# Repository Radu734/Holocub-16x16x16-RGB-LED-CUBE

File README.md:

# **Holocub V2 – 16×16×16 RGB LED Cube**

*A fully addressable 3D LED display for animations, games, and visual effects.*

---

## 📜 Overview
Holocub V2 is a large-scale **16×16×16 RGB LED cube** (4096 voxels total) built with WS2812B addressable LEDs.  
It is designed to display dynamic animations, interactive effects, and data visualizations in 3D.

The cube is controlled by a microcontroller (planned: **RPi Pico 2W / other capable MCU**) and supports both **procedural animations** and **pre-rendered frames** loaded from an SD card.

---

## 🔧 Hardware Specifications

| Component                     | Specification |
|--------------------------------|---------------|
| **Cube Size**                 | 16 × 16 × 16 voxels |
| **Total LEDs**                | 4096 WS2812B RGB LEDs |
| **LED Type**                  | WS2812B (5V, individually addressable) |
| **PSUs**                      | 4 × 5v 350w |
| **Data Lines**                | One per 16×16 vertical layer (16 total) |
| **LED Strip Arrangement**     | Snake layout per layer (serpentine wiring) |
| **MCU**                       | Raspberry Pi Pico 2W (planned) / Teensy 4.1 (more power but no internal BLE and wifi) |
| **Storage**                   | MicroSD card (frame/animation storage) |
| **Power Injection**           | Multiple injection points per strip |
| **Estimated Max Power**       | ~1.23 kW at full white (theoretical max) |

---

# HoloBoard – PCB by Dragoș

**Short description**  
HoloBoard is a custom PCB designed for the Holocub project, acting as the main control and interface board.  
It hosts a Raspberry Pi Pico 2W, integrates a piezo buzzer, and features two bidirectional logic-level shifters for for the communication between the pico and the WS2812B as 3v3 logic could cause interference.

## 🔧 Key Features
- **MCU Slot:** Raspberry Pi Pico 2W header footprint (solder-in or socket).
- **Audio Output:** 1 × piezo buzzer connector (with optional series resistor).
- **Expandable hardware:** Left over pins (used mainly for I²C and SPI) routed to the side for extra connectivity.
- **Build Quality:** Silk labels for pins, test pads, and mounting holes.
- **Filter capacitors:** 2 filter caps for main power connection and 1 for each logic level shofter for optimal data transmission without interference.

## 📦 Minimal BOM
- 1 × RP2040 (Pico 2W) socket / header footprint
- Headers, pads, mounting hardware
- Yet to add more info

---

## 📜 Schematics & Photos

### **Schematic – Level Shifter**
  
*Figure 1 — The HoloBoard schematic in KeyCad.*

### **Schematic – Power & Buzzer**
  
*Figure 2 — components used, I/O's, connections.*

### **Photo – Assembled (Front)**
  
*Figure 3 — Front view, Pico 2W inserted.*

### **Photo – Assembled (Back / Solder Side)**
  
*Figure 4 — Back view showing soldering and Logo.*

---

## 🚀 Features
- **Scalable architecture** – animations work on both 4×4×4 test cube and full 16×16×16 cube. 
- **Voxel-based rendering** – uses a global `voxelMatrix[x][y][z]` buffer for color control.
- **Procedural animations** – gradients, bouncing “DVD logo” effect, rain simulation, waves.
- **Pre-rendered playback** – read `.vox` file for animations or custom binary format.
- **Custom GFX library** – draw lines, planes, waves, text in 3D space.
- **SD card support** – load animations without reflashing firmware.
- **Multi-PSU design** – independent PSU per cube tower for stable power delivery.
- **Website based animation upload and debug** - Upload animations or images directly from a computer to the Holocube.

---

## ⚡ Power & Safety Notes
- WS2812B LEDs consume up to **60 mA per LED** at full brightness (white).
- Theoretical maximum current: **~245 A total** across 4 PSUs.
- Always fuse PSU outputs and use thick wiring for high-current paths.
- Avoid running full white at 100% brightness for prolonged periods to reduce heat.

---

## 🖥️ Software Workflow
### **Procedural animations**
- Written in C++ inside `/animations`
- Rendered directly to `voxelMatrix`
- Useful for dynamic effects and parameterized visuals

### **Pre-rendered animations**
- Created in Paint, MagicaVoxel, or similar tools
- Exported as `.bmp` or custom `.hca` (Holocub Animation) binary format
- Loaded via SD card at runtime

---

## 📸 Development Timeline
- **Phase 1** – Test code, Custom PCB `HoloBoard`, SD card reader on 4×4×4 cube ✅
- **Phase 2** – Develop GFX & cube configuration libraries ✅
- **Phase 3** – Build cube structure & solder all LED strips 🔄
- **Phase 4** – Integrate procedural + SD-based playback
- **Phase 5** – Optimize power, stability, and animation library

---

## 🛠️ Setup & Build
### **Dependencies**
- [Adafruit NeoPixel](https://github.com/adafruit/Adafruit_NeoPixel)
- SD card library for chosen MCU
- C++17 compatible toolchain
- PlatformIO (recommended) or Arduino IDE

### **Compilation**
```bash
# PlatformIO
pio run --target upload
```

### **Arduino IDE**
- Install Adafruit NeoPixel library
- Select **Raspberry Pi Pico 2W** (or your MCU)
- Upload `src/main.ino`

---

## 📄 License
[MIT License](LICENSE) – You are free to use, modify, and distribute this project with attribution.

---

## 🙌 Credits
- **Core team:** [Bernea Dragoș Dada & Teodosiu Radu]
- **Special thanks:** MaltWiskey (inspiration & reference designs), Adafruit (NeoPixel library) and the C++ community.
- **Open Source softwares used for the cube animations:** MagicaVoxel (3D sprites designer)

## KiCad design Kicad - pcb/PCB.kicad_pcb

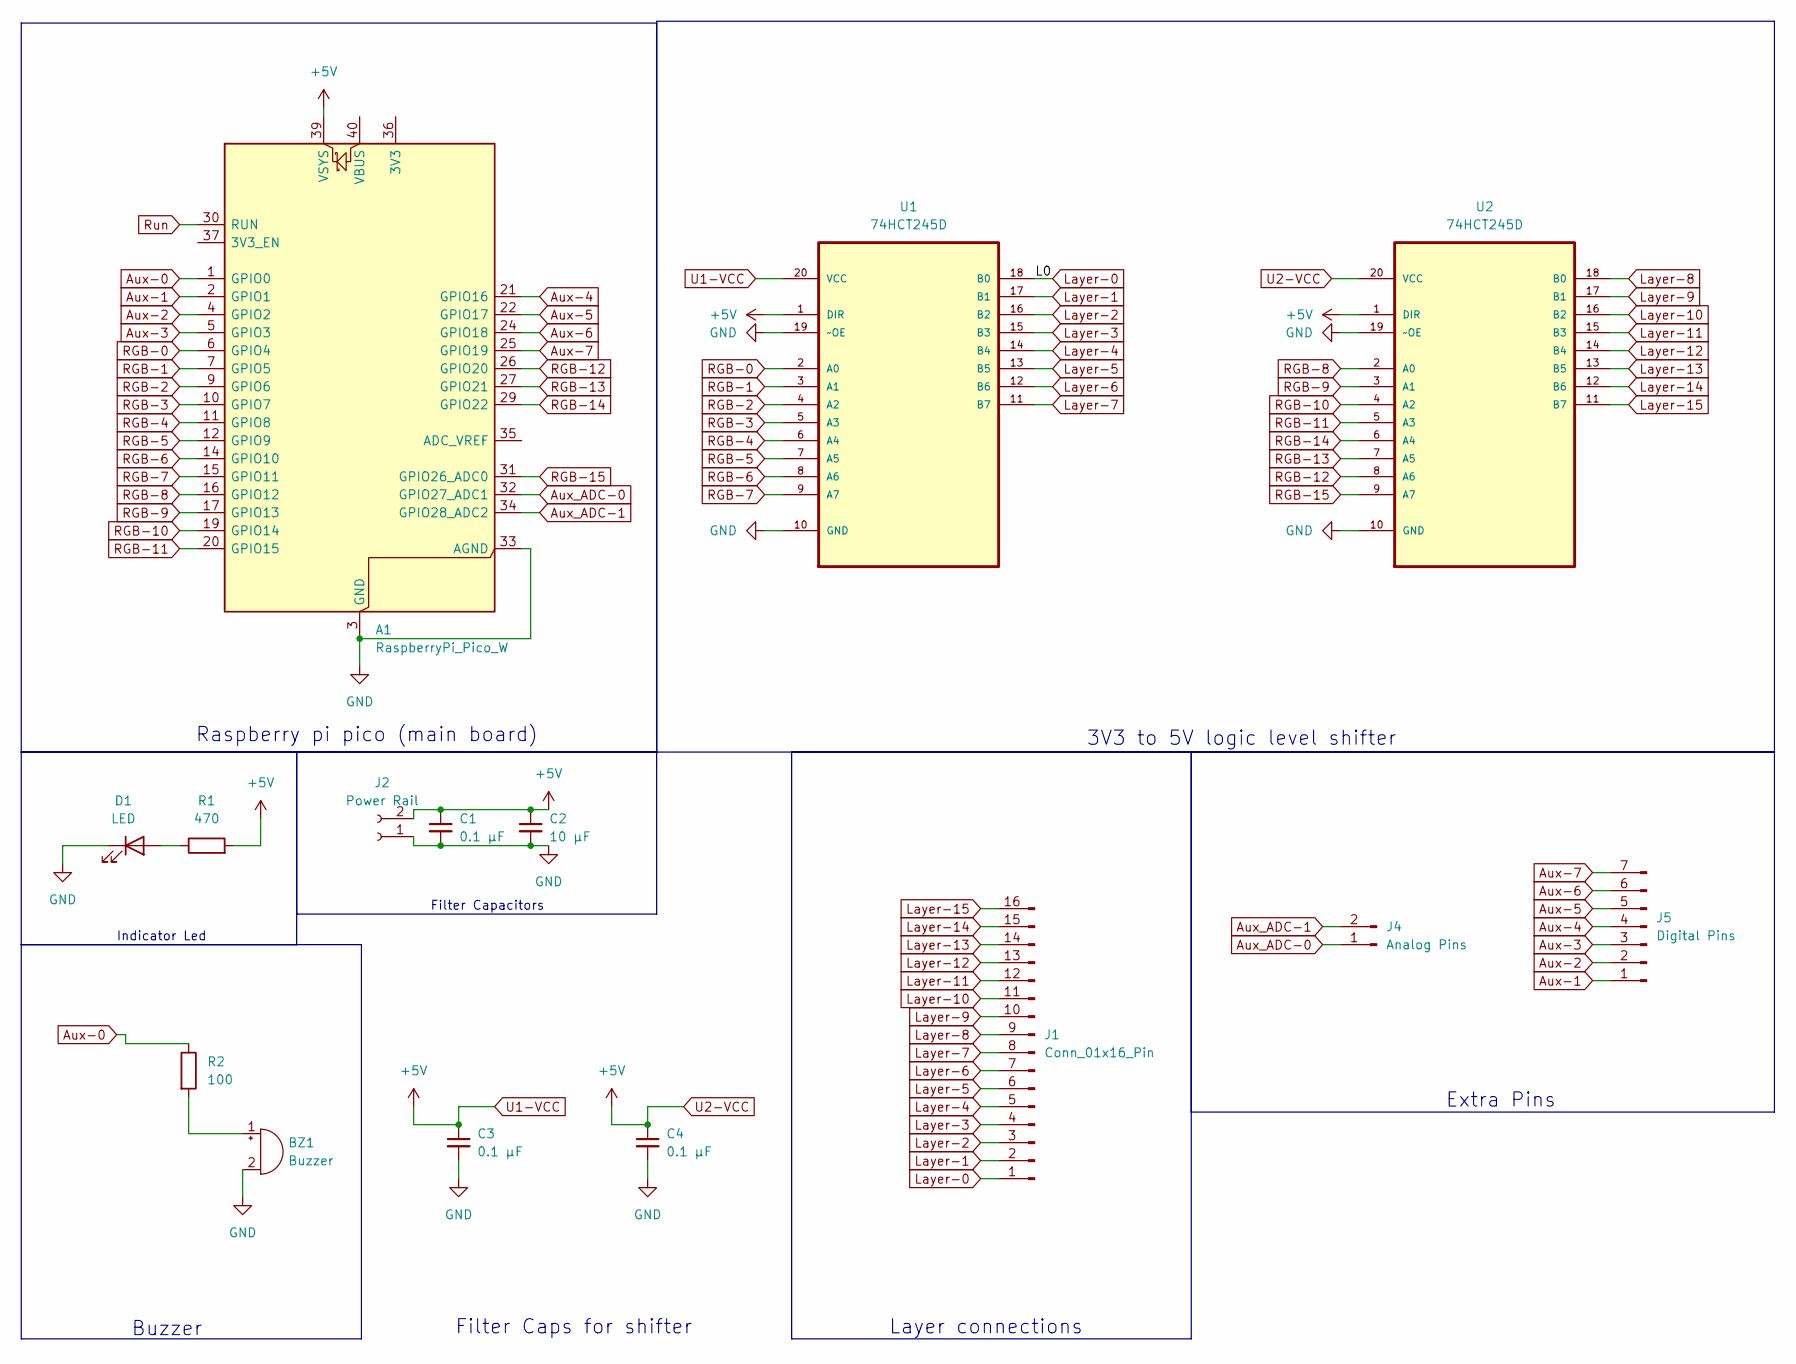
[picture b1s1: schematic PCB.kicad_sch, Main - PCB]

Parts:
A1: RaspberryPi_Pico_W; RaspberryPi_Pico_Common_THT
BZ1: Buzzer; Buzzer_12x9.5RM7.6
C1: 0.1 µF; C_0603_1608Metric
C2: 10 µF; C_1206_3216Metric
C3, C4: 0.1 µF; C_0201_0603Metric
D1: LED; LED_0603_1608Metric_Pad1.05x0.95mm_HandSolder
J1: Conn_01x16_Pin; PinHeader_1x16_P2.54mm_Vertical
J2: Power Rail; PinHeader_1x02_P2.54mm_Vertical
J4: Analog Pins; PinHeader_1x02_P2.54mm_Vertical
J5: Digital Pins; PinHeader_1x07_P2.54mm_Vertical
R1: 470; R_0201_0603Metric
R2: 100; R_0603_1608Metric
U1, U2: 74HCT245D; SOIC127P1032X265-20N; MPN 74HCT245D

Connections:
Aux-0: A1.1 (GPIO0), R2.1
Aux-1: A1.2 (GPIO1), J5.1
Aux-2: A1.4 (GPIO2), J5.2
Aux-3: A1.5 (GPIO3), J5.3
Aux-4: A1.21 (GPIO16), J5.4
Aux-5: A1.22 (GPIO17), J5.5
Aux-6: A1.24 (GPIO18), J5.6
Aux-7: A1.25 (GPIO19), J5.7
Aux_ADC-0: A1.32 (GPIO27_ADC1), J4.1
Aux_ADC-1: A1.34 (GPIO28_ADC2), J4.2
GND: A1.3 (GND), A1.8 (GND), A1.13 (GND), A1.18 (GND), A1.23 (GND), A1.28 (GND), A1.33 (AGND), A1.38 (GND), BZ1.2 (-), C1.2, C2.2, C3.2, C4.2, D1.1 (K), J2.1, U1.10 (GND), U1.19 (~OE), U2.10 (GND), U2.19 (~OE)
Layer-0: J1.1, U1.18 (B0)
Layer-1: J1.2, U1.17 (B1)
Layer-2: J1.3, U1.16 (B2)
Layer-3: J1.4, U1.15 (B3)
Layer-4: J1.5, U1.14 (B4)
Layer-5: J1.6, U1.13 (B5)
Layer-6: J1.7, U1.12 (B6)
Layer-7: J1.8, U1.11 (B7)
Layer-8: J1.9, U2.18 (B0)
Layer-9: J1.10, U2.17 (B1)
Layer-10: J1.11, U2.16 (B2)
Layer-11: J1.12, U2.15 (B3)
Layer-12: J1.13, U2.14 (B4)
Layer-13: J1.14, U2.13 (B5)
Layer-14: J1.15, U2.12 (B6)
Layer-15: J1.16, U2.11 (B7)
unnamed: BZ1.1 (+), R2.2
unnamed: D1.2 (A), R1.1
RGB-0: A1.6 (GPIO4), U1.2 (A0)
RGB-1: A1.7 (GPIO5), U1.3 (A1)
RGB-2: A1.9 (GPIO6), U1.4 (A2)
RGB-3: A1.10 (GPIO7), U1.5 (A3)
RGB-4: A1.11 (GPIO8), U1.6 (A4)
RGB-5: A1.12 (GPIO9), U1.7 (A5)
RGB-6: A1.14 (GPIO10), U1.8 (A6)
RGB-7: A1.15 (GPIO11), U1.9 (A7)
RGB-8: A1.16 (GPIO12), U2.2 (A0)
RGB-9: A1.17 (GPIO13), U2.3 (A1)
RGB-10: A1.19 (GPIO14), U2.4 (A2)
RGB-11: A1.20 (GPIO15), U2.5 (A3)
RGB-12: A1.26 (GPIO20), U2.8 (A6)
RGB-13: A1.27 (GPIO21), U2.7 (A5)
RGB-14: A1.29 (GPIO22), U2.6 (A4)
RGB-15: A1.31 (GPIO26_ADC0), U2.9 (A7)
Run: A1.30 (RUN)
U1-VCC: A1.39 (VSYS), C1.1, C2.1, C3.1, C4.1, J2.2, R1.2, U1.1 (DIR), U1.20 (VCC), U2.1 (DIR), U2.20 (VCC)

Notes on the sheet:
Extra Pins
3V3 to 5V logic level shifter
Filter Caps for shifter
Indicator Led
Filter Capacitors
Layer connections
Buzzer
Raspberry pi pico (main board)

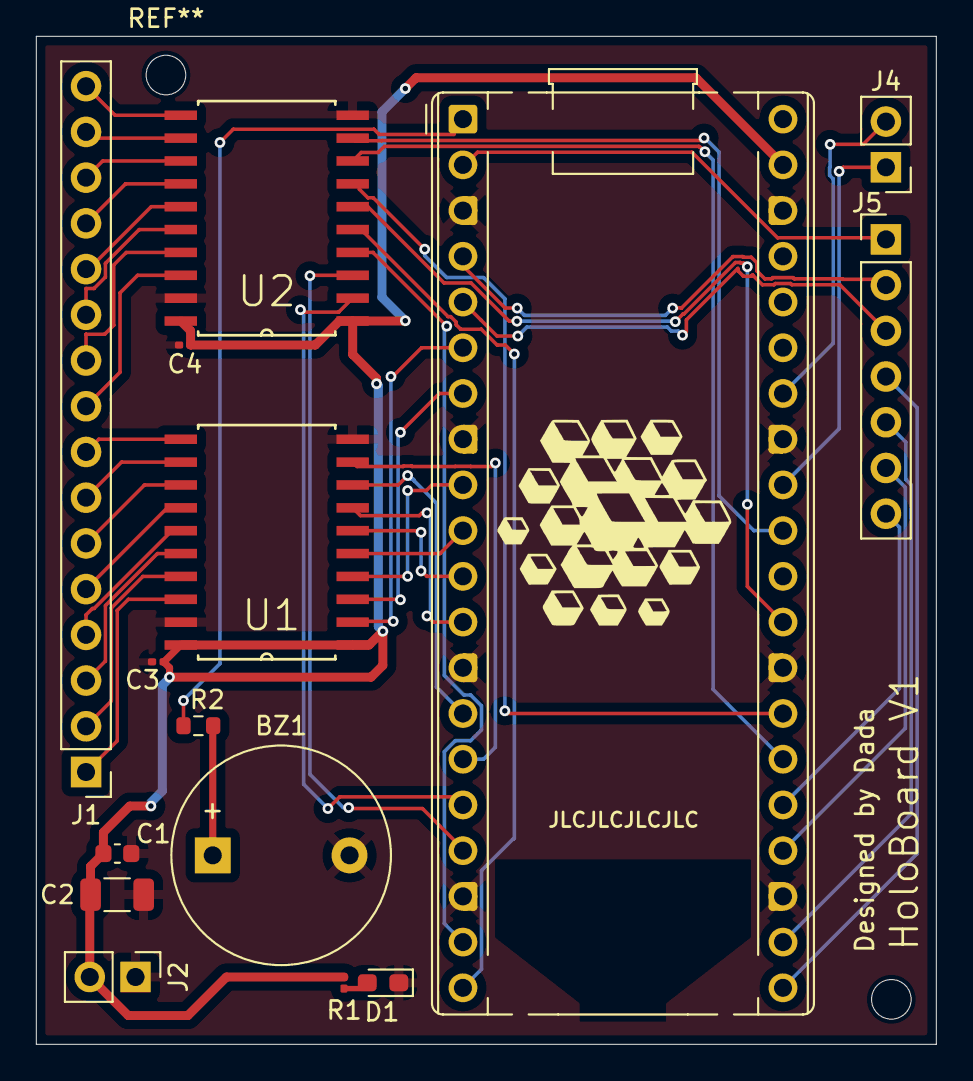
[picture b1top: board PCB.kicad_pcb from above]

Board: 4 copper layers, 50.0 x 56.0 mm, 15 parts (0 on the bottom side), 46 nets.

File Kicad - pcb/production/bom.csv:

Designator,Footprint,Quantity,Value,LCSC Part #
A1,RaspberryPi_Pico_Common_THT,1,RaspberryPi_Pico_W,
BZ1,Buzzer_12x9.5RM7.6,1,Buzzer,
C1,0603,1,0.1 µF,
C2,1206,1,10 µF,
"C3, C4",0201,2,0.1 µF,
D1,0603,1,LED,
J1,PinHeader_1x16_P2.54mm_Vertical,1,Conn_01x16_Pin,
J2,PinHeader_1x02_P2.54mm_Vertical,1,Power Rail,
J4,PinHeader_1x02_P2.54mm_Vertical,1,Analog Pins,
J5,PinHeader_1x07_P2.54mm_Vertical,1,Digital Pins,
R1,0201,1,470,
R2,0603,1,100,
"U1, U2",SOIC127P1032X265-20N,2,74HCT245D,74HCT245D

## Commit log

2025-08-10 init
2025-08-10 Created LICENCE & README
2025-08-10 Added HoloBoard mention Into README
2025-08-10 Fixed Images not showing in README
2025-08-11 refactor: moved animations to header files fixed: animations giving errors if the "cube" is not a cube
2025-08-11 fix: removed dynamic allocation of strips and replaced it with extern variables in CubeConfig.h
2025-08-13 feat: added drawCube function, 44 errors found because of redeclaration of CubeConfig & CubeTypes
2025-08-17 Added PCB Gerber Files
2025-08-19 feat: added SD card Initialisation & Reading
2025-09-03 feat: added support for the rp pico 2W
2026-03-30 Add Compressed Gif
2026-03-30 Replace video link with GIF for LED Cube example
    Updated the LED Cube example image to a GIF format.
2026-03-30 Update core team names in credits section
2026-03-30 Update credits and software references in README
